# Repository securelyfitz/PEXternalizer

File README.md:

PEXternalizer
=============

Pci Express eXternalizer lets you pull a PCIE1x port outside of your case using a usb3 cable

## Theory

PCI Express is a pretty awesome interface that excels at 'just working' no matter how bad a job your board/device was designed.

It automatically detects and enumerates devices, and automatically connects to them with as many lanes (X's) as possible at the highest speed possible (1.0=2.5ghz, 2.0=5ghz, 3.0=8ghz)

Due to this flexibility, you can plug a 1X card into a 16x slot, and vice versa, so long as you can physically make it fit (dremels, drills, saws, etc... now that's HARDWARE hacking)

PEXternalizer will allow you to plug one a tiny PCIE card into a slot on your board, and run a cable out of the box to a second PCB with a PCIE 1x slot on it.
The PCIE SIG specs external cabling for PCIE but it's too expensive. Luckily, there's a readily available inexpensive consumer cable rated for one 500mhz pair and 2 5ghz pairs : a USB 3.0 cable.

I designed it to fit in 50x50mm for DFRobot. They don't permit two boards in one design, so i just silkscreened a dotted line where you have to cut it in half. (more HARDWARE hacking)

##Using

* Disconnect power to your system
* Plug the PCIE fingers into a slot on your board.
* Plug a USB 3.0 A-Male to A-Male cable in the board (preferably 12", though i've gotten it to work up to 3')
* Run the cable wherever it needs to go and plug it in the other board.
* Plug your PCIe card in the slot. You might want to use zip ties to hold the board on to your card.
* Power up and cross your fingers!

##Building
Rev 0.9 is off to the fab, but of course not yet tested!

The Digikey BOM is saved in PEXternalizer-BOM.csv, you can upload or paste it's contents into the BOM wizard: https://www.digikey.com/classic/registereduser/BOMWizard.aspx

$7.01 + shipping

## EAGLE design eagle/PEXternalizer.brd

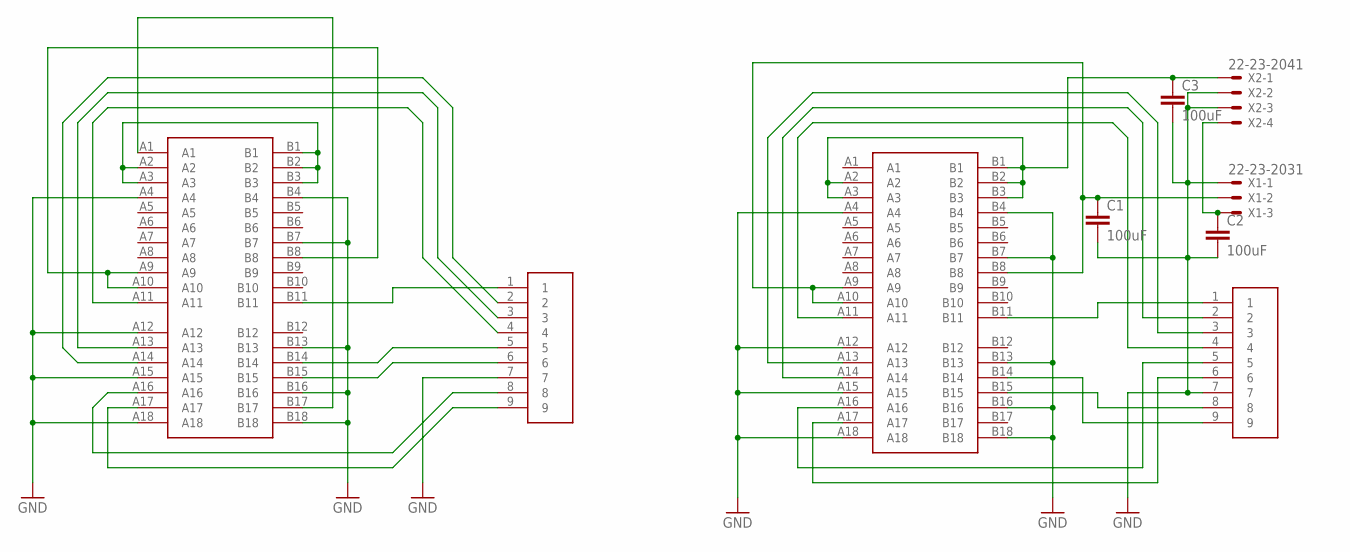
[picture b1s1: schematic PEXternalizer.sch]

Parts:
3.3V: PCI-E1XEDGE; PCI-E_36_EDGE
3.3V1: PCI-E1XCONN; PCI-E_36_CONN
C1, C2: 100uF; C5B2.5
C3: 100uF; C2.5-2
U$1, U$2: USB3FLAT; USB3_FLAT
X1: 22-23-2031
X2: 22-23-2041

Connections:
3.3V: 3.3V.A9, 3.3V.A10, 3.3V.B8
3.3V1: 3.3V1.A9, 3.3V1.A10, 3.3V1.B8, C1.1, X1.2
12V: 3.3V.A2, 3.3V.A3, 3.3V.B1, 3.3V.B2, 3.3V.B3
12V1: 3.3V1.A2, 3.3V1.A3, 3.3V1.B1, 3.3V1.B2, 3.3V1.B3, C3.1, X2.1
CLK2_N: 3.3V1.A14, U$2.2
CLK2_P: 3.3V1.A13, U$2.3
CLK_N: 3.3V.A13, U$1.3
CLK_P: 3.3V.A14, U$1.2
GND: 3.3V.A4, 3.3V.A12, 3.3V.A15, 3.3V.A18, 3.3V.B4, 3.3V.B7, 3.3V.B13, 3.3V.B16, 3.3V.B18, 3.3V1.A4, 3.3V1.A12, 3.3V1.A15, 3.3V1.A18, 3.3V1.B4, 3.3V1.B7, 3.3V1.B13, 3.3V1.B16, 3.3V1.B18, C1.2, C2.2, C3.2, U$1.7, U$2.7, X1.1, X2.2, X2.3
unnamed: 3.3V.B11, U$1.1
unnamed: 3.3V.A1, 3.3V.B17
unnamed: 3.3V1.A11, U$2.4
unnamed: 3.3V1.B11, U$2.1
unnamed: C2.1, X1.3, X2.4
unnamed: 3.3V.A11, U$1.4
RX1_N: 3.3V.A16, U$1.8
RX1_P: 3.3V.A17, U$1.9
RX2_N: 3.3V1.A16, U$2.5
RX2_P: 3.3V1.A17, U$2.6
TX1_N: 3.3V.B14, U$1.5
TX1_P: 3.3V.B15, U$1.6
TX2_N: 3.3V1.B15, U$2.8
TX2_P: 3.3V1.B14, U$2.9

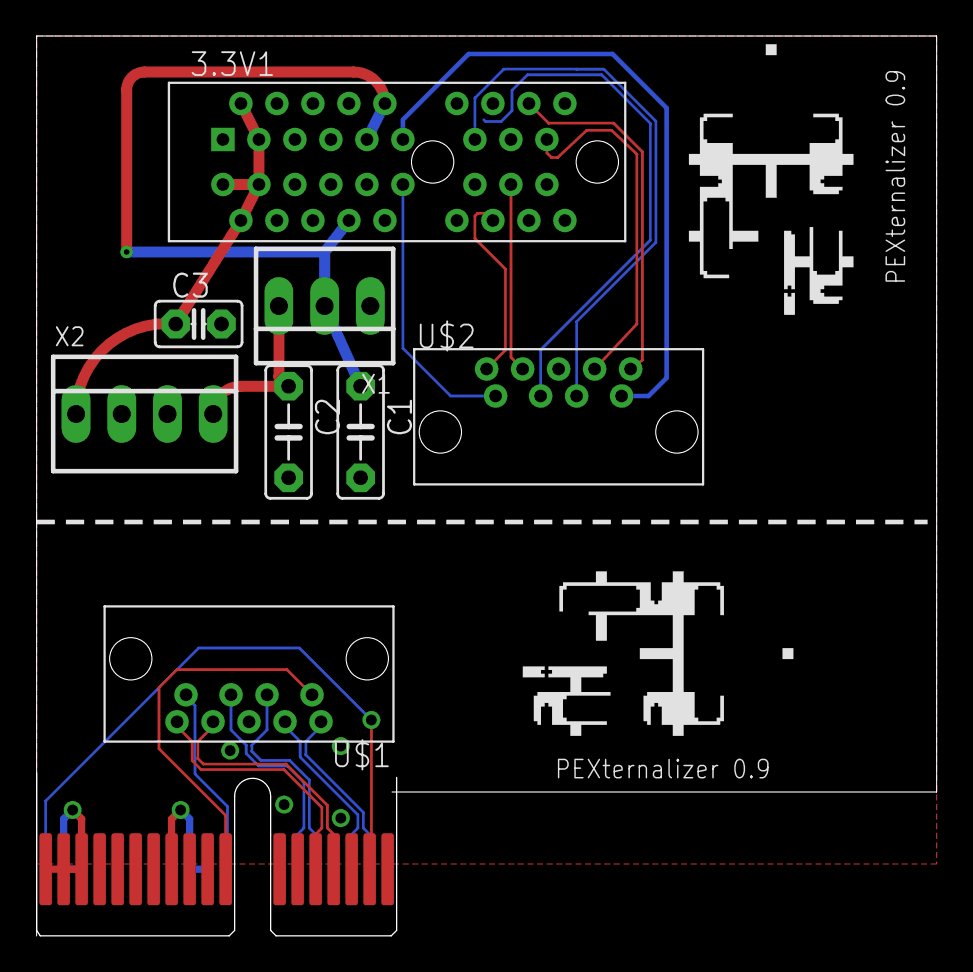
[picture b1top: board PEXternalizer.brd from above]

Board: 2 copper layers, 50.0 x 50.0 mm, 11 parts (0 on the bottom side), 23 nets.

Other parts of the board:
U$3, U$4: SH

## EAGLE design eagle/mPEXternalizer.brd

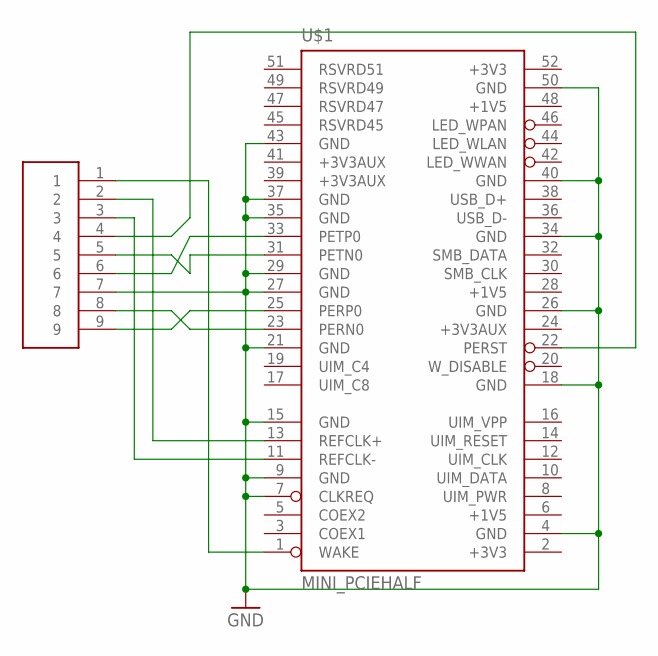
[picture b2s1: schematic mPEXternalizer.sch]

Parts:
U$1: MINI_PCIEHALF; MINI_PCIE_HALF
U$2: USB3FLAT; USB3_FLAT

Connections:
+1V5: U$1.6 (+1V5), U$1.28 (+1V5)
+3V3: U$1.2 (+3V3), U$1.52 (+3V3)
+3V3AUX: U$1.24 (+3V3AUX)
CK_N: U$1.11 (REFCLK-), U$2.3
CK_P: U$1.13 (REFCLK+), U$2.2
GND: U$1.4 (GND), U$1.7 (CLKREQ), U$1.9 (GND), U$1.15 (GND), U$1.18 (GND), U$1.21 (GND), U$1.26 (GND), U$1.27 (GND), U$1.29 (GND), U$1.34 (GND), U$1.35 (GND), U$1.37 (GND), U$1.40 (GND), U$1.43 (GND), U$1.50 (GND), U$1.HOLE1B (GND), U$1.HOLE1T (GND), U$1.HOLE2B (GND), U$1.HOLE2T (GND), U$2.7
unnamed: U$1.1 (WAKE), U$2.1
unnamed: U$1.22 (PERST), U$2.4
RX_N: U$1.25 (PERP0), U$2.9
RX_P: U$1.23 (PERN0), U$2.8
SMB_DATA: U$1.32 (SMB_DATA)
TX_N: U$1.31 (PETN0), U$2.5
TX_P: U$1.33 (PETP0), U$2.6
USB_D+: U$1.38 (USB_D+)

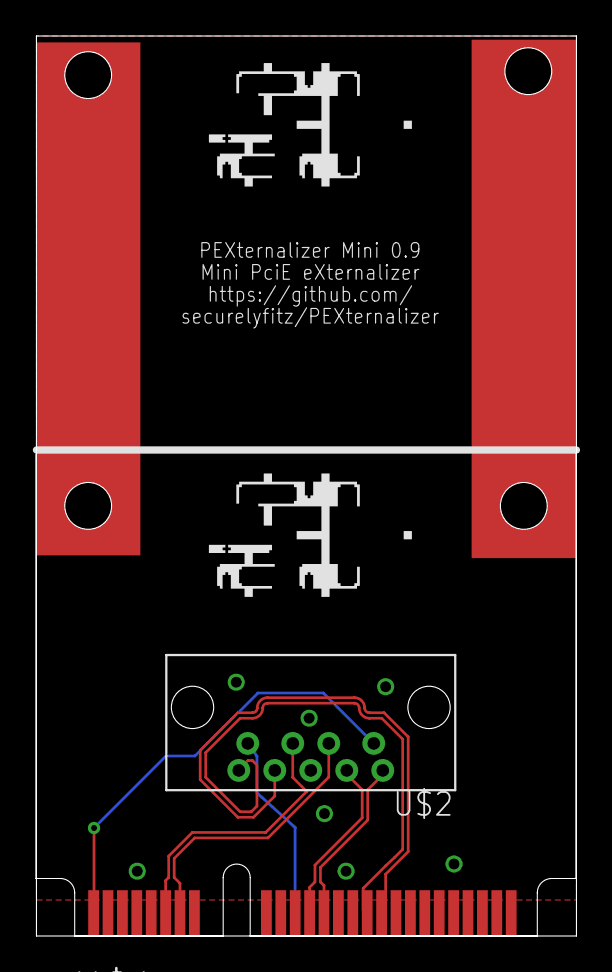
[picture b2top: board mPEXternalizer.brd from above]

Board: 2 copper layers, 30.0 x 50.0 mm, 4 parts (0 on the bottom side), 11 nets.

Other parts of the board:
U$3, U$4: SH-HALFINCH

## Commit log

2013-11-27 Adding board files
2013-11-27 fixing filenames
2013-11-27 silkscreen edits
2013-11-27 added usb2 connector
2013-11-27 Adding mini pci version
2013-11-28 Fixed stupid board error.
    overlapping power plane traces fixed!
